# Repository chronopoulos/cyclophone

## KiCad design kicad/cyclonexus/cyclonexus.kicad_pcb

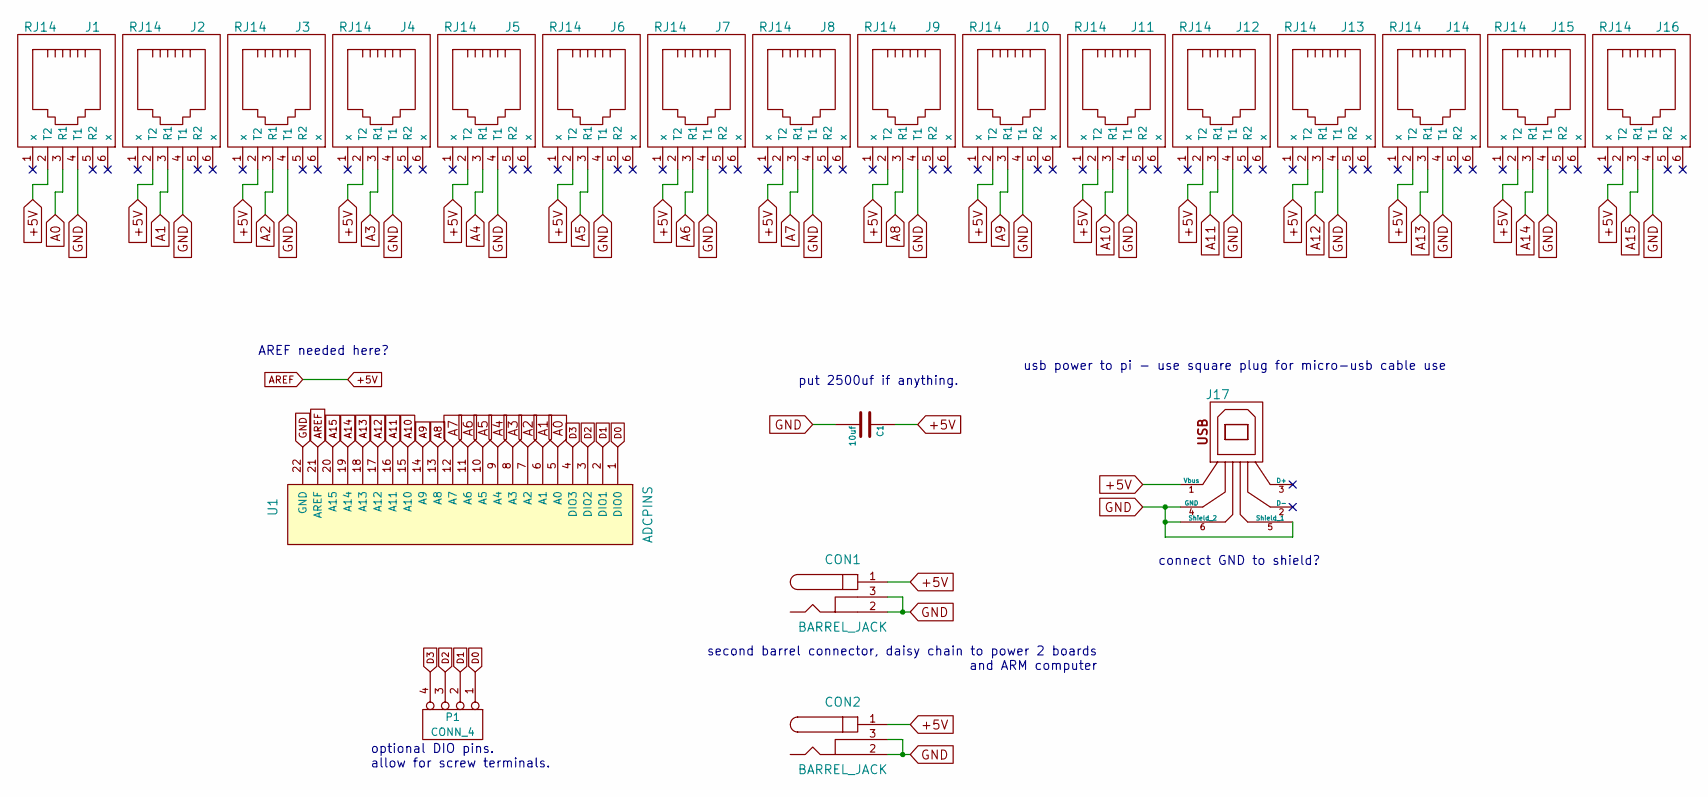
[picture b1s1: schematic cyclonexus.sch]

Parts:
C1: 10uf
CON1, CON2: BARREL_JACK
J1, J2, J3, J4, J5, J6, J7, J8, J9, J10, J11, J12, J13, J14, J15, J16: RJ14
J17: USB_1
P1: CONN_4
U1: ADCPINS

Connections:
+5V: C1.1, CON1.1, CON2.1, J1.2 (T2), J2.2 (T2), J3.2 (T2), J4.2 (T2), J5.2 (T2), J6.2 (T2), J7.2 (T2), J8.2 (T2), J9.2 (T2), J10.2 (T2), J11.2 (T2), J12.2 (T2), J13.2 (T2), J14.2 (T2), J15.2 (T2), J16.2 (T2), J17.1 (Vbus), U1.21 (AREF)
A0: J1.3 (R1), U1.5 (A0)
A1: J2.3 (R1), U1.6 (A1)
A2: J3.3 (R1), U1.7 (A2)
A3: J4.3 (R1), U1.8 (A3)
A4: J5.3 (R1), U1.9 (A4)
A5: J6.3 (R1), U1.10 (A5)
A6: J7.3 (R1), U1.11 (A6)
A7: J8.3 (R1), U1.12 (A7)
A8: J9.3 (R1), U1.13 (A8)
A9: J10.3 (R1), U1.14 (A9)
A10: J11.3 (R1), U1.15 (A10)
A11: J12.3 (R1), U1.16 (A11)
A12: J13.3 (R1), U1.17 (A12)
A13: J14.3 (R1), U1.18 (A13)
A14: J15.3 (R1), U1.19 (A14)
A15: J16.3 (R1), U1.20 (A15)
D0: P1.1, U1.1 (DIO0)
D1: P1.2, U1.2 (DIO1)
D2: P1.3, U1.3 (DIO2)
D3: P1.4, U1.4 (DIO3)
GND: C1.2, CON1.2, CON1.3, CON2.2, CON2.3, J1.4 (T1), J2.4 (T1), J3.4 (T1), J4.4 (T1), J5.4 (T1), J6.4 (T1), J7.4 (T1), J8.4 (T1), J9.4 (T1), J10.4 (T1), J11.4 (T1), J12.4 (T1), J13.4 (T1), J14.4 (T1), J15.4 (T1), J16.4 (T1), J17.4 (GND), J17.5 (Shield_1), J17.6 (Shield_2), U1.22 (GND)

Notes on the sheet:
AREF needed here?
usb power to pi - use square plug for micro-usb cable use
put 2500uf if anything.
second barrel connector, daisy chain to power 2 boards and ARM computer
connect GND to shield?
optional DIO pins. allow for screw terminals.

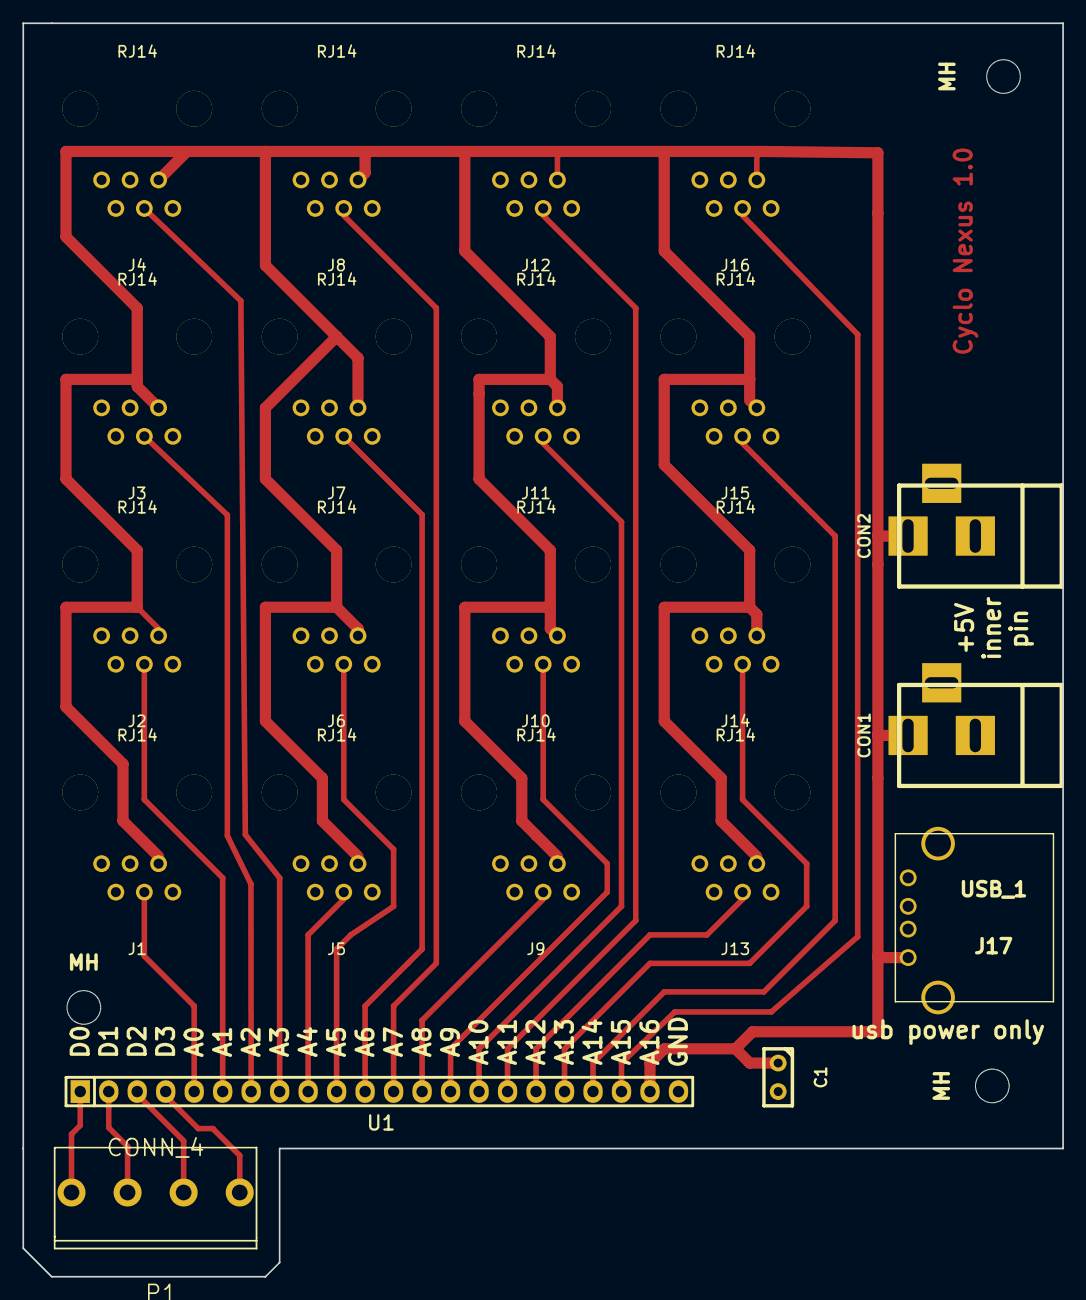
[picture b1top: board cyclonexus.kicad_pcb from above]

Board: 2 copper layers, 92.7 x 111.8 mm, 25 parts (0 on the bottom side), 22 nets.

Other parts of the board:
MH: MountingHole_3mm_RevA_Date21Jun2010; MountingHole_3mm
MH#2, MH#3: MountingHole_3mm_RevA_Date21Jun2010; MountingHole_3mm

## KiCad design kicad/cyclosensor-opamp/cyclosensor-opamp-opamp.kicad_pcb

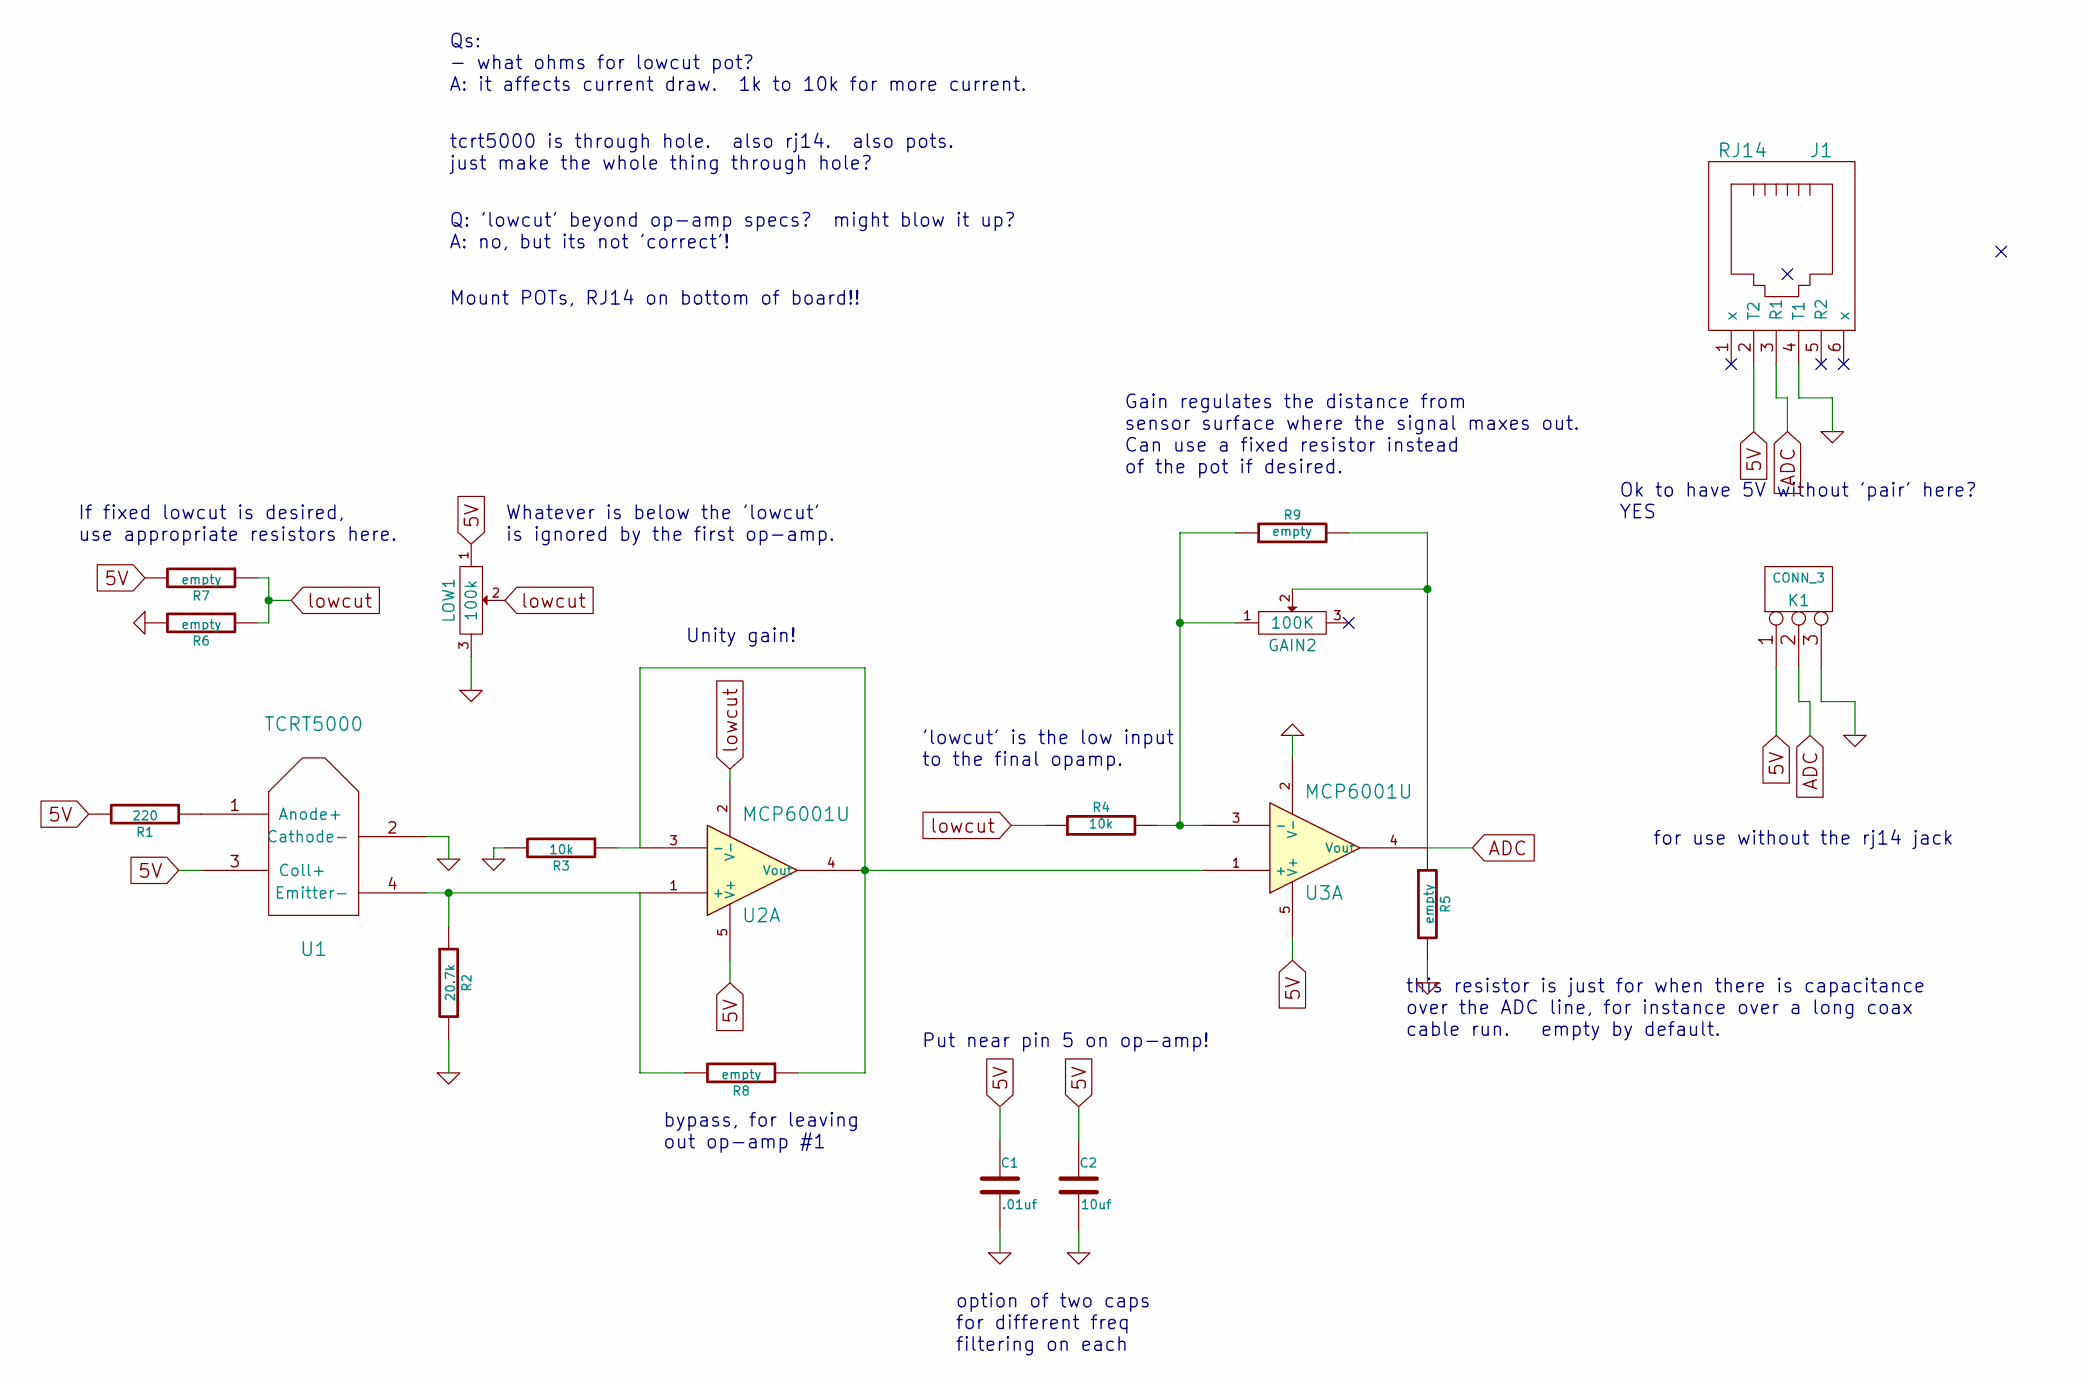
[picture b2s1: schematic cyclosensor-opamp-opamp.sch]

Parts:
C1: .01uf
C2: 10uf
GAIN2: 100K
J1: RJ14
K1: CONN_3
LOW1: 100k
R1: 220
R2: 20.7k
R3: 10k
R4: 10k
R5: empty
R6, R7, R8, R9: empty
U1: TCRT5000
U2, U3: MCP6001U

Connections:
5V: C1.1, C2.1, J1.2 (T2), K1.1, LOW1.1, R1.2, R7.2, U1.3 (Coll+), U2.5 (V+), U3.5 (V+)
ADC: GAIN2.2, J1.3 (R1), K1.2 (PM), R5.1, R9.2, U3.4 (Vout)
GND: C1.2, C2.2, J1.4 (T1), K1.3, LOW1.3, R2.2, R3.2, R5.2, R6.2, U1.2 (Cathode-), U3.2 (V-)
unnamed: GAIN2.1, R4.2, R9.1, U3.3 (-)
unnamed: R1.1, U1.1 (Anode+)
unnamed: R2.1, R8.2, U1.4 (Emitter-), U2.1 (+)
unnamed: R3.1, R8.1, U2.3 (-), U2.4 (Vout), U3.1 (+)
lowcut: LOW1.2, R4.1, R6.1, R7.1, U2.2 (V-)

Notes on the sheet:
Ok to have 5V without 'pair' here? YES
Put near pin 5 on op-amp!
option of two caps for different freq filtering on each
Unity gain!
Whatever is below the 'lowcut' is ignored by the first op-amp.
'lowcut' is the low input to the final opamp.
Gain regulates the distance from sensor surface where the signal maxes out. Can use a fixed resistor instead of the pot if desired.
for use without the rj14 jack
this resistor is just for when there is capacitance over the ADC line, for instance over a long coax cable run. empty by default.
If fixed lowcut is desired, use appropriate resistors here.
Qs: - what ohms for lowcut pot? A: it affects current draw. 1k to 10k for more current.
tcrt5000 is through hole. also rj14. also pots. just make the whole thing through hole?
Q: 'lowcut' beyond op-amp specs? might blow it up? A: no, but its not 'correct'!
Mount POTs, RJ14 on bottom of board!!
bypass, for leaving out op-amp #1

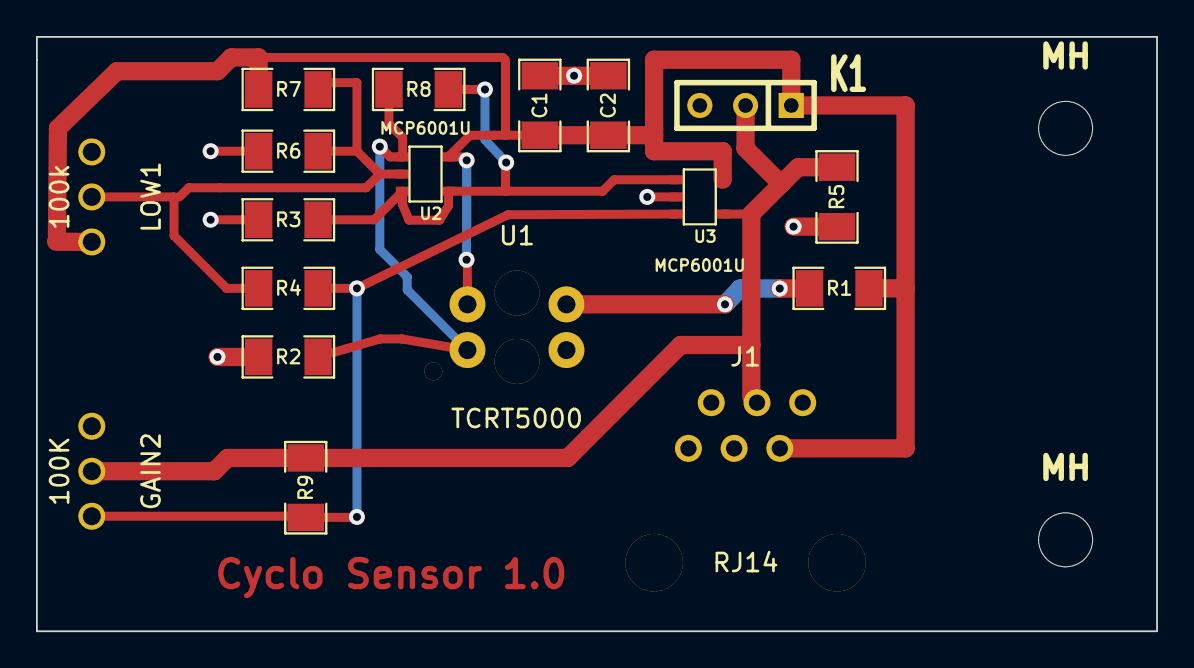
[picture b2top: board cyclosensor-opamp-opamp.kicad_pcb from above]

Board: 2 copper layers, 62.2 x 33.0 mm, 20 parts (0 on the bottom side), 8 nets.

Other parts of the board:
MH: MountingHole_3mm_RevA_Date21Jun2010; MountingHole_3mm
MH#2: MountingHole_3mm_RevA_Date21Jun2010; MountingHole_3mm

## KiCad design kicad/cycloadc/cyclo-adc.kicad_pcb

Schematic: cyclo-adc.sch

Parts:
ADC-0, ADC-1: ADS7957
C1: C
IOPINS0: ADC-0-PINS
IOPINS1: ADC-1-PINS
P1, P2: CONN_8
R1: 2K
U1: TL431LP

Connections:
3.3V: ADC-0.36 (+VBD), ADC-1.36 (+VBD), P1.2, P2.2, R1.1
+AREF: ADC-0.5 (+VA), ADC-0.29 (+VA), ADC-1.5 (+VA), ADC-1.29 (+VA), IOPINS0.21 (AREF), IOPINS1.21 (AREF), P1.1, P2.1
CH0: ADC-0.28 (CH0), IOPINS0.5 (A0)
CH1: ADC-0.27 (CH1), IOPINS0.6 (A1)
CH2: ADC-0.26 (CH2), IOPINS0.7 (A2)
CH3: ADC-0.25 (CH3), IOPINS0.8 (A3)
CH4: ADC-0.24 (CH4), IOPINS0.9 (A4)
CH5: ADC-0.23 (CH5), IOPINS0.10 (A5)
CH8: ADC-0.18 (CH8), IOPINS0.13 (A8)
CH9: ADC-0.17 (CH9), IOPINS0.14 (A9)
CH10: ADC-0.16 (CH10), IOPINS0.15 (A10)
CH11: ADC-0.15 (CH11), IOPINS0.16 (A11)
CH12: ADC-0.14 (CH12), IOPINS0.17 (A12)
CH13: ADC-0.13 (CH13), IOPINS0.18 (A13)
CH14: ADC-0.12 (CH14), IOPINS0.19 (A14)
CH15: ADC-0.11 (CH15), IOPINS0.20 (A15)
CH16: ADC-1.28 (CH0), IOPINS1.5 (A16)
CH17: ADC-1.27 (CH1), IOPINS1.6 (A17)
CH18: ADC-1.26 (CH2), IOPINS1.7 (A18)
CH19: ADC-1.25 (CH3), IOPINS1.8 (A19)
CH20: ADC-1.24 (CH4), IOPINS1.9 (A20)
CH21: ADC-1.23 (CH5), IOPINS1.10 (A21)
CH24: ADC-1.18 (CH8), IOPINS1.13 (A24)
CH25: ADC-1.17 (CH9), IOPINS1.14 (A25)
CH26: ADC-1.16 (CH10), IOPINS1.15 (A26)
CH27: ADC-1.15 (CH11), IOPINS1.16 (A27)
CH28: ADC-1.14 (CH12), IOPINS1.17 (A28)
CH29: ADC-1.13 (CH13), IOPINS1.18 (A29)
CH30: ADC-1.12 (CH14), IOPINS1.19 (A30)
CH31: ADC-1.11 (CH15), IOPINS1.20 (A31)
CS0: ADC-0.31 (CS), P1.8, P2.8
CS1: ADC-1.31 (CS), P1.7, P2.7
DIO0: ADC-0.37 (GPIO0), IOPINS0.1 (DIO0)
DIO1: ADC-0.38 (GPIO1), IOPINS0.2 (DIO1)
DIO2: ADC-0.1 (GPIO2), IOPINS0.3 (DIO2)
DIO3: ADC-0.2 (GPIO3), IOPINS0.4 (DIO3)
DIO4: ADC-1.37 (GPIO0), IOPINS1.1 (DIO4)
DIO5: ADC-1.38 (GPIO1), IOPINS1.2 (DIO5)
DIO6: ADC-1.1 (GPIO2), IOPINS1.3 (DIO6)
DIO7: ADC-1.2 (GPIO3), IOPINS1.4 (DIO7)
GND: ADC-0.3 (REFM), ADC-0.6 (AGND), ADC-0.9 (AINM), ADC-0.10 (AGND), ADC-0.19 (AGND), ADC-0.20 (AGND), ADC-0.30 (AGND), ADC-0.35 (BDGND), ADC-1.3 (REFM), ADC-1.6 (AGND), ADC-1.9 (AINM), ADC-1.10 (AGND), ADC-1.19 (AGND), ADC-1.20 (AGND), ADC-1.30 (AGND), ADC-1.35 (BDGND), C1.2, IOPINS0.22 (GND), IOPINS1.22 (GND), P1.3, P2.3, U1.3 (A)
unnamed: ADC-0.7 (MXO), ADC-0.8 (AINP)
unnamed: ADC-1.7 (MXO), ADC-1.8 (AINP)
REFP: ADC-0.4 (REFP), ADC-1.4 (REFP), C1.1, R1.2, U1.1 (K), U1.2 (R)
SCLK: ADC-0.32 (SCLK), ADC-1.32 (SCLK), P1.6, P2.6
SDI: ADC-0.33 (SDI), ADC-1.33 (SDI), P1.5, P2.5
SDO: ADC-0.34 (SDO), ADC-1.34 (SDO), P1.4, P2.4

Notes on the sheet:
Identical pinouts for both. Should face opposite directions on layout, to allow using two of the same daughtercard, one for each set of pins.
bypass cap here? 2.5 to ground
Added re Dan
could leave cap empty
normally jumper pins 1 and 2 for 0 to 5v range.
screw terminal spacing.

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
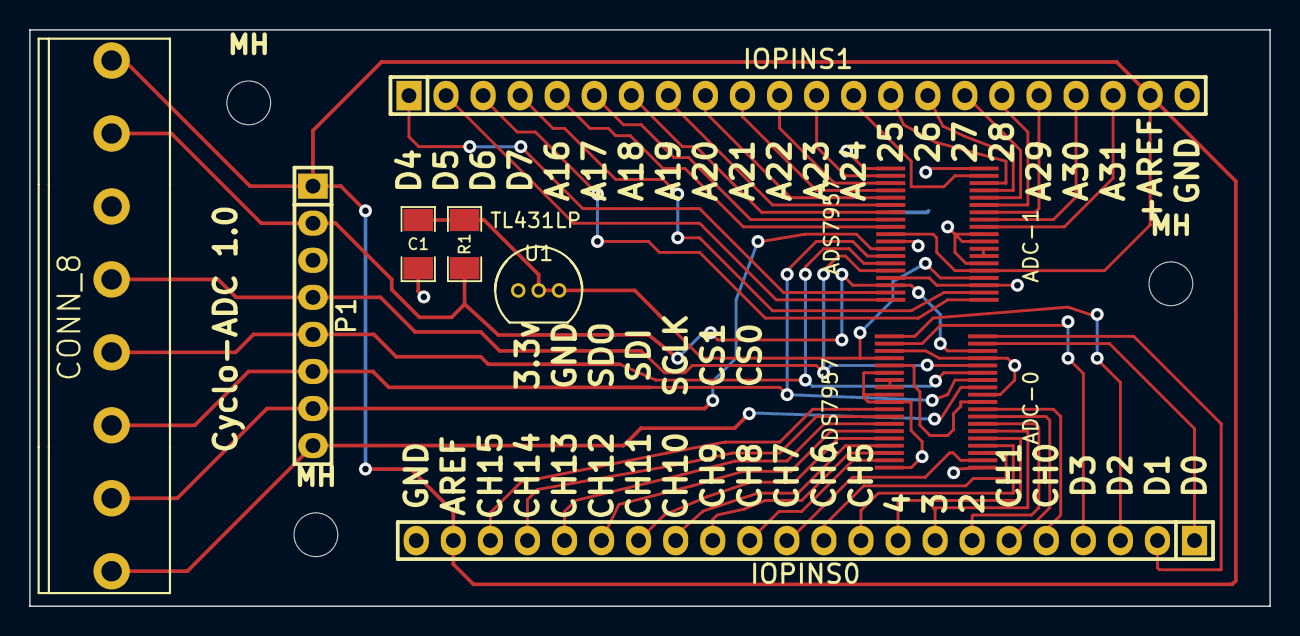
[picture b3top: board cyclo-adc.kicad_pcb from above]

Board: 2 copper layers, 85.0 x 39.5 mm, 12 parts (0 on the bottom side), 51 nets.

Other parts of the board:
MH: MountingHole_3mm_RevA_Date21Jun2010; MountingHole_3mm
MH#2, MH#3: MountingHole_3mm_RevA_Date21Jun2010; MountingHole_3mm

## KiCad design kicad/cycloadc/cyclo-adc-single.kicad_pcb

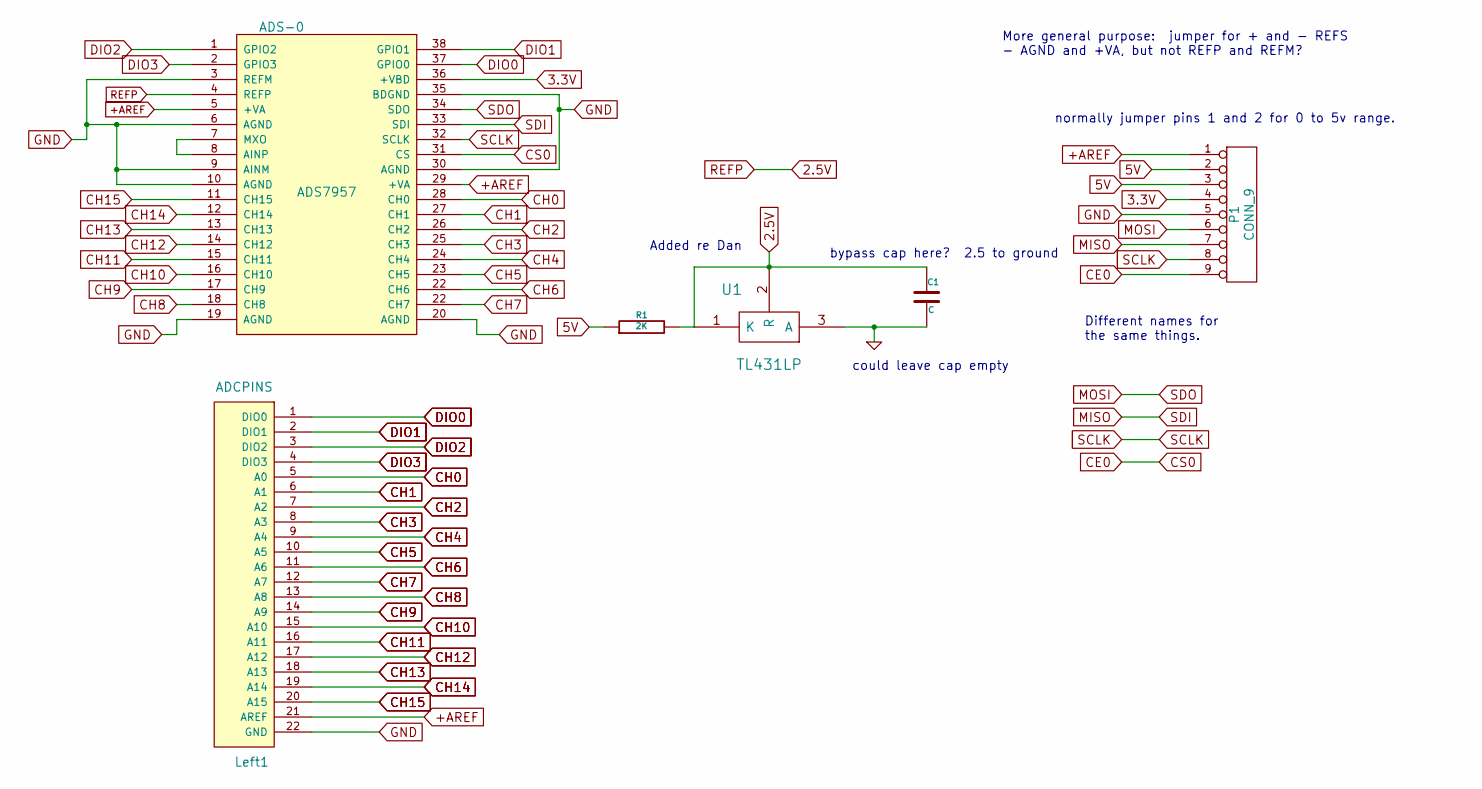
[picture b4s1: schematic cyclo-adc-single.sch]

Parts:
ADS-0: ADS7957
C1: C
Left1: ADCPINS
P1: CONN_9
R1: 2K
U1: TL431LP

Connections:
3.3V: ADS-0.36 (+VBD), P1.4
5V: P1.2, P1.3, R1.1
+AREF: ADS-0.5 (+VA), ADS-0.29 (+VA), Left1.21 (AREF), P1.1
CE0: ADS-0.31 (CS), P1.9
CH0: ADS-0.28 (CH0), Left1.5 (A0)
CH1: ADS-0.27 (CH1), Left1.6 (A1)
CH2: ADS-0.26 (CH2), Left1.7 (A2)
CH3: ADS-0.25 (CH3), Left1.8 (A3)
CH4: ADS-0.24 (CH4), Left1.9 (A4)
CH5: ADS-0.23 (CH5), Left1.10 (A5)
CH8: ADS-0.18 (CH8), Left1.13 (A8)
CH9: ADS-0.17 (CH9), Left1.14 (A9)
CH10: ADS-0.16 (CH10), Left1.15 (A10)
CH11: ADS-0.15 (CH11), Left1.16 (A11)
CH12: ADS-0.14 (CH12), Left1.17 (A12)
CH13: ADS-0.13 (CH13), Left1.18 (A13)
CH14: ADS-0.12 (CH14), Left1.19 (A14)
CH15: ADS-0.11 (CH15), Left1.20 (A15)
DIO0: ADS-0.37 (GPIO0), Left1.1 (DIO0)
DIO1: ADS-0.38 (GPIO1), Left1.2 (DIO1)
DIO2: ADS-0.1 (GPIO2), Left1.3 (DIO2)
DIO3: ADS-0.2 (GPIO3), Left1.4 (DIO3)
GND: ADS-0.3 (REFM), ADS-0.6 (AGND), ADS-0.9 (AINM), ADS-0.10 (AGND), ADS-0.19 (AGND), ADS-0.20 (AGND), ADS-0.30 (AGND), ADS-0.35 (BDGND), C1.2, Left1.22 (GND), P1.5, U1.3 (A)
unnamed: ADS-0.7 (MXO), ADS-0.8 (AINP)
REFP: ADS-0.4 (REFP), C1.1, R1.2, U1.1 (K), U1.2 (R)
SCLK: ADS-0.32 (SCLK), P1.8
SDI: ADS-0.33 (SDI), P1.7
SDO: ADS-0.34 (SDO), P1.6

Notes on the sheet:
Different names for the same things.
bypass cap here? 2.5 to ground
Added re Dan
could leave cap empty
More general purpose: jumper for + and - REFS - AGND and +VA, but not REFP and REFM?
normally jumper pins 1 and 2 for 0 to 5v range.

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
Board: 2 copper layers, 6 parts (0 on the bottom side), 29 nets, no tracks yet.

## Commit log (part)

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2014-03-30 'fix' initial 'baseline' by using a delay.
2014-03-30 configurable print/sendOSC for key presses.
2014-03-30 tweak print options a bit.
2014-04-01 notes
2014-04-01 rewrite to use one big word per adc instead of 2 byte words per sensor.
2014-04-01 going back to non-big-word mode!
    Revert "fixes to just print values. send mode not working right now."
    This reverts commit 24172cb15d74ab9f29424005258f601f11f90d18.
2014-04-01 add the 'bigword' version of keyosc for later reference perhaps. code not used!
2014-04-06 various changes to schematics
2014-04-06 updating basic cyclo-sensor. Still need to verify with actual cyclophone.
2014-04-09 various changes! notes frm Dan.
2014-04-13 more changes to match current test circuit.
2014-04-13 remove PI pins, power regulator thingy, add optional DIO connector.
2014-04-16 tweak a few things
2014-04-22 add the noninverting opamp design
2014-04-25 tweak opamp circuit to match reality. added dual opamp circuit for low/high adjustments to sensor range.
2014-04-25 tweaks to the opamp-opamp circuit. remove extra unused stuff. about ready to move to the layout stage.
2014-04-27 pcb design is semi-complete! looks that way, anyway.
2014-04-29 add mounting holes
2014-04-30 redo of adc board with thicker traces, caps next to adc chips.
2014-04-30 a few more tweaks.
2014-05-01 add the gerbers that were sent out for printing.
2014-05-02 make "diffFormat = False" actually work
2014-05-02 extensive changes to keyosc. not working yet.
2014-05-03 remove merge junk, wups
2014-05-07 can play a single sound from osc message...
2014-05-12 add some extra stuff here
2014-05-13 remove dead code.
2014-05-16 rename, add start.sh for keyosc
2014-05-17 hopefully sending osc messages again
2014-05-17 print osc messages that are sent.
2014-05-17 variable osc number based on (x / 1024)
2014-05-18 commnts
2014-05-19 print or send depending on prefs
2014-05-20 mega-restructure of everything. separate update and IO ftns, Input datatype.
2014-05-20 velocity stuff
2014-05-20 maxes
2014-05-20 add toggle command
2014-05-21 fix maxprint
2014-05-21 fix outwrite
2014-05-21 duration message to outfile.
2014-05-22 add velmax mode
2014-05-22 toggleVelMax
2014-05-22 fix velmax
2014-05-22 non-niceprint
2014-05-22 hopefully good max position peak find.
2014-05-23 new max algo
2014-05-23 machine and human readable outwrite formats
2014-05-25 change from csound to sdl for sample playback.
2014-05-25 allow IPs besides 127.0.0.1
2014-05-26 add 'soundtest'
2014-05-26 build script for debian; notes
2014-05-26 serialtest prog.
2014-05-26 add the over-thres-continuous-send mode
2014-05-26 add continuous mode.
2014-05-27 fix continously varying volume. It works!
2014-05-27 change existing sound instead of making new one every time
2014-05-27 try halt instead of fadeout
2014-05-27 comment out debug prints
2014-05-27 works with the arduino now!
2014-05-28 velposmax algo - experimental
2014-05-28 first stab at ftns for running the pd patch
2014-05-28 import bytestring as 'B'
2014-05-29 multi thread code for serial port
2014-05-29 move junk into the junkyard.
2014-05-30 updated cabal file to go with previous changes.
2014-05-30 serialtest works multithreaded now
2014-05-31 add serialtest2 - using System.Serial and hReady to test readiness.
2014-05-31 cpp program that reads the serial port.
2014-05-31 rename nolomain to cyclosensors.cpp; add some serial code.
2014-05-31 serial and sensors simultaneously. stop the 'take over stdio' behavior so ctrl-c works.
2014-05-31 rename to main.cpp
2014-06-01 'velposmax' algo basically working.
2014-06-01 stuff wired up, compiling
2014-06-01 implement arduino command parse.
2014-06-01 init cyclomap on create; add correct IP address for OSC
2014-06-01 fix scale calculation.
2014-06-01 delay time from 0 to 1000
2014-06-01 added apo2014 folder with dronezone (brainwaves) patch
2014-06-02 fix init problem with StartNote
2014-06-02 fix scales.
2014-06-02 wups, installed keys backwards. plus, wierd problem with key ordering. fixed.
2014-06-02 got brainwave OSC input to work cleanly in parallel with eeg data
2014-06-03 add 'dynamic baseline' gadget. doesn't work that well yet!
2014-06-04 add 'startcyclosensors.sh'
2014-06-04 print baselines every 1000 readings, in addition to diffs.
2014-06-09 'OnContinuous' ftn.
2014-06-11 adjust key thres, change IP address of sound server.
2014-06-11 configurable IP address and port in settings.
2014-06-11 increase gain
2014-06-11 require threshold crossing before another key hit is allowed.
2014-06-17 move keyosc to new location.
2014-06-17 change lib location
2014-06-18 continuous mode
2014-06-19 works, sort of. samples play but no volume adjustment yet.
2014-06-19 send 'keye' message on key end; rename some things.
2014-06-19 handle key-end message
2014-06-19 continuous mode fix.
2014-06-20 add some test code.
2014-06-20 add test7.hs for raspberry pi test
2014-06-20 add a reset at program start.
2014-06-20 switch to USB sound device. is better!
2014-06-22 change from max/min to variance for evaluating whether to dynamically change the baseline for a key. should be way more efficient, but need to test to determine good values to use.
2014-06-23 update for new variance algo
2014-06-23 debugging; change from playing samples to sinoscs for test.
2014-06-23 remove comments
2014-06-23 change back to sample playback instead of sinosc. works!
2014-06-24 play to other stereo channel for subwoofer.
2014-06-24 first stab at a sample pack mapfile
2014-06-24 fixes. works!
2014-06-25 changes for a list of samplemaps instead of just one. index through the maps using knob 0.
2014-06-25 remove / from msgs to keep things consistent.
2014-06-25 add 'multimap' file, with 2 maps.
2014-06-26 fix interpolation
2014-06-26 add other mellotron sounds except for violins.
2014-06-26 stuff for trying to run jack without alsa_out. alsa_out adds 10% cpu
2014-06-27 send key hits too
2014-06-27 add stuff for scoscandir, change indexing in sampmap a little.
2014-06-28 fix relative directory thing, sort of.
2014-06-28 if 'hit' mode, don't kill the sound on keyend.
2014-06-29 first try at mapping scales onto sample sets.
2014-06-30 fix buffer map
2014-06-30 scale, transpose knob working, with some quirks.
2014-07-04 make paths relative to sample directory and not absolute.
2014-07-07 add attempt at delay with feedback.
2014-07-07 config delay time with knob 2
2014-07-07 make delay feedback configuration - make button 0 == 'alt' knob 2 = delay time knob 2 + alt = delay feedback
2014-07-08 change to slightly less artifact-y delayC from delayN
2014-07-08 add code for looping. doesn't work yet!
2014-07-08 move buffer create to before synthdefs.
2014-07-09 try passing phasor output to another synthdef through bus; didn't work.
2014-07-10 add ftns to allow changing scale, root note through osc.
2014-07-11 add some messages indicating what's going on with scales and etc when they change.
2014-07-11 more loop attempts
2014-07-15 yay reset works now! back to the buffer beginning!
2014-07-16 remove failed looper code
2014-07-16 add these... really old and dunno if any good.
2014-07-21 changes to key map algo - allow multiple 'soundbanks' and then have multiple key layouts that use those soundbanks.
    also, load all samples at program start instead of reloading samples from disk each time.
2014-07-22 convert things to double to make compiler happy on pcduino
2014-08-03 first pass at assigning LED colors to pitches.
2014-08-03 use map file in cyclophone_samples dir.
2014-08-05 decrease led intensity; use withTransport to close udp sockets after use.
2014-08-05 subract out the root before updating LEDs with scale.:wq
2014-08-06 map colors to correct keys. seems to work!
2014-08-06 fix, so working better from /etc/rc.local
2014-08-12 remove old mapfiles; change main.hs so compiles
2014-08-13 update LEDs when scale or root msg received. comment out print statements
2014-08-13 add example 'song' that changes cyclophone tonality on a schedule.
2014-08-17 remove debug code from LED send. add -O to cabal ghc options.
2014-08-18 fix delay knob issue
2014-08-18 add 'inactive threshold' feature, for keys that take a little while to resume their original positions.
2014-08-23 done
2014-10-06 synth map working!!
2014-10-06 more toFreq more generic.
2014-10-06 connect synths to the gSynthOut bus, for delay and etc.
2014-10-31 ada led controller...
2014-11-01 add some install notes; start jackd and scsyth using screen so I can look at their error msgs.
2014-11-01 notready note.
2014-11-02 new settings, for new ip with wrtnode.
2014-11-29 getspi script, just documenting how to get spi device to show up.
2014-12-03 change to compile on banana pi
2014-12-03 banana pi startup scripts.
2014-12-03 rc.local from banana pi
2014-12-04 simple commands for making color arrays and switching between them.
2014-12-05 remove dead code, comments, etc. fix by resizing things to be within the limited arduino memory (2K).
2014-12-05 semi working interp. only from low to high vals.
2014-12-05 replace Serial.print with a macro.
2014-12-06 add sort-of-working oscadaleds program.
2014-12-06 turn off debug messages. works much better without them!
2014-12-06 fix fading.
2014-12-07 make serial port configurable in prefs.
2014-12-07 update bananapi start scripts.
2014-12-07 test files for the osc led server
2014-12-07 add tremsaw, tremsine
2014-12-10 make the lowest note seriously lowwq
2014-12-12 5.8 ms latency on bananapi/creative soundblaster. pretty good!
2014-12-22 update .nix, comments
2014-12-30 switch to 192.168.8.174 for bananapi.
2015-02-06 add license file to oscadaleds
2015-05-10 print current time on osc message received.
2015-06-04 gitignore update
2015-06-04 pitchshifting works!
2015-06-04 downgrade stuff to work with ghc 7.4
2015-06-05 add nix stuff
2015-06-05 might as well save this
2015-06-05 call various setup ftns inside 'do' instead of separate withSC3 calls.
2015-06-05 some stuff from attempting audio input. commented for later.
2015-06-05 script to kill all the cyclophone processes
2015-06-06 more wierd tunings
2015-07-01 move bananapi stuff to subdir
2015-07-03 move pcduino stuff to subdir.
2015-08-22 print message with basic info when running
2015-08-22 mod script for new file locations
2015-09-02 simple rust project to recieve/send osc msgs.
2015-09-02 receiving, sending msgs.
2015-09-02 creating a new message
2015-09-05 rename startup scripts for bananapi
2015-09-05 changes to adjust volume from cyclophone.
2015-09-05 add some faust stuff
2015-09-05 add code snippet for faust-alsa cmdline args
2015-09-06 more faust patches
2015-09-12 partly working systemd services; other startup tweaks:
2015-09-18 print message when sending osc.
2015-09-18 various changes for debugging startup problems
2015-09-18 notes for testing faust progs
2015-09-19 systemd service file that works, just not at bootup.
2015-12-06 optional settings file argument
2015-12-06 remove title, add 5 way switch
2015-12-06 comments/indention
2015-12-06 misc odds and ends
2015-12-10 keythread, for pushing the sliders back up to home position after being pressed.
2015-12-10 process all update messages each round, instead of only one per round.
2015-12-14 fix key messages
2015-12-30 improvements for key stuff
2016-02-21 remove unnecessary html file.
2016-02-21 switch over to building buf as needed; implement unpress.
2016-02-22 portaudio version of cyclofraust
2016-02-28 address change
2016-04-04 cyclofraust_alsa
2016-04-04 maybe lowest period size for this adapter
2016-05-08 remove other cyclofraust versions - now are branches in cyclofraust repo
2016-06-03 VolHit keytype, maybe for lower latency drums
2016-06-05 prog to find max excursion of keys, write to array.
2016-06-05 cyclomaxes for key range calibration
2016-06-05 use 0.0.0.0 for generic IP receiving
2016-10-14 add labels for things, change prefs for oscpad 0.2.1
2016-12-31 partway towards key recording and playback
2016-12-31 recording toggle v0.001
2017-02-26 light hoop sketch for the cyclo-dome!
